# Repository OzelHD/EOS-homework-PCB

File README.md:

# Generation complete!
# EOS Homework Board

This board is a tutorial follow-along for the EOS homework assignment. It is designed to be a simple board that can be used to learn about PCB design and manufacturing. [Layout Video](https://www.youtube.com/watch?v=nkHFoxe0mrU), [PCB video](https://www.youtube.com/watch?v=PlXd3lLZ4vc)
:)
# Include documentation here

The documentation can be very similar to your wiki article

#Getting started

use `git submodule init && git submodule update --remote --recursive` to get the submodules, and then you can use the project as a normal KiCAD project.

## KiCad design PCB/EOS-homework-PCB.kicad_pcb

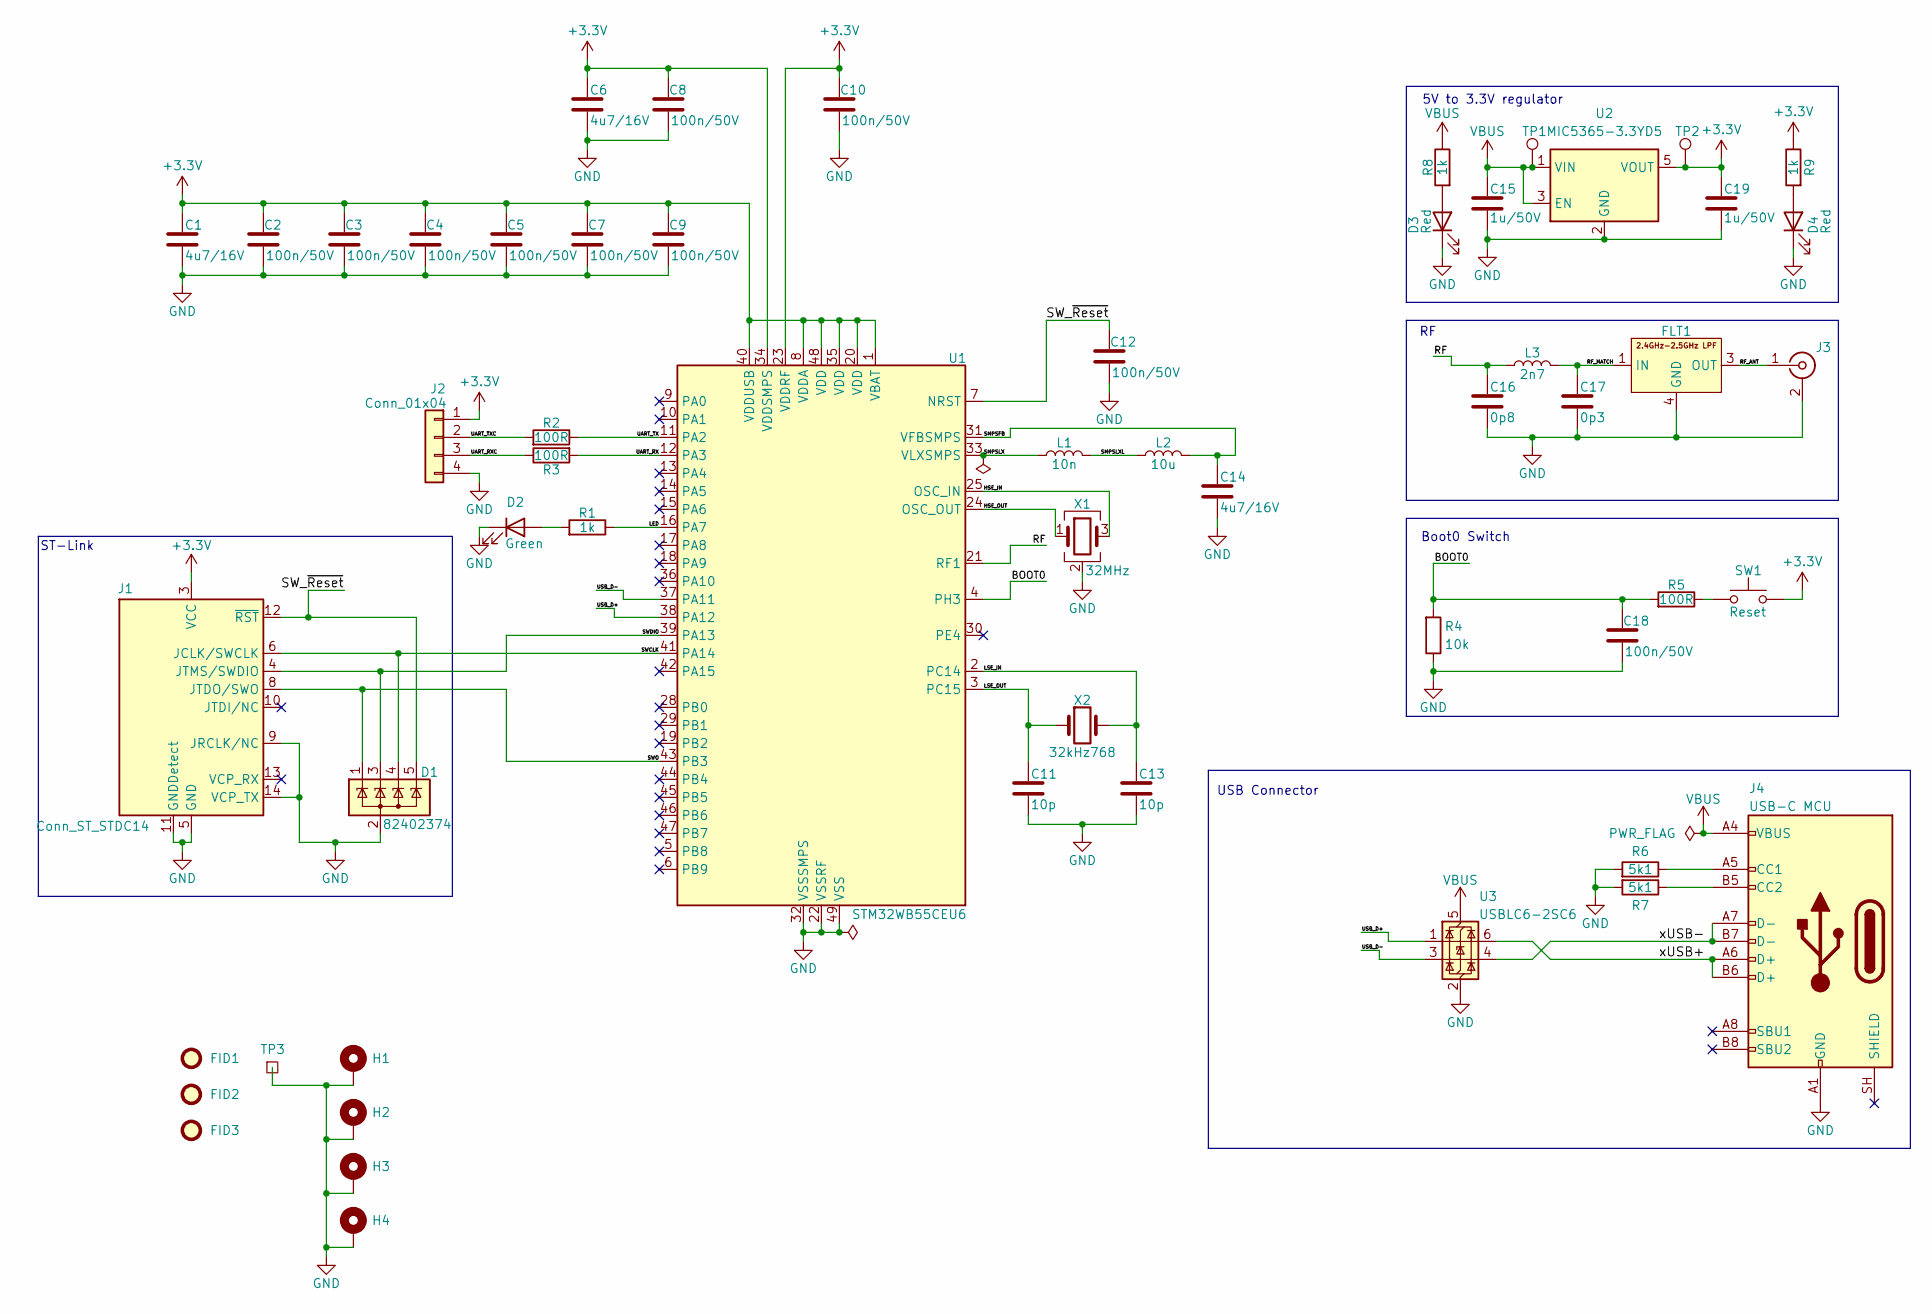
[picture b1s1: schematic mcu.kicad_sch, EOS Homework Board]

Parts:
C1, C6, C14: 4u7/16V; C_0805_2012Metric; Part No. 885012207053
C2, C3, C4, C5, C7, C8, C9, C10, C12, C18: 100n/50V; C_0603_1608Metric; Part No. 885012206095
C11, C13: 10p; C_0603_1608Metric
C15, C19: 1u/50V; C_0603_1608Metric; Part No. 885012206126
C16: 0p8; C_0603_1608Metric
C17: 0p3; C_0603_1608Metric
D1: 82402374; SOT-353_SC-70-5; Part No. 82402374
D2: Green; LED_0603_1608Metric; Part No. 150060GS75000
D3, D4: Red; LED_0603_1608Metric; Part No. 150060RS75000
FID1, FID2, FID3: Fiducial; Fiducial_1mm_Mask2mm
FLT1: DLF162500LT-5028A1
H1, H2, H3, H4: MountingHole_Pad; MountingHole_2.2mm_M2_Pad_Via
J1: Conn_ST_STDC14; IDC-Header_2x07_P1.27mm_Vertical_SMD; Part No. 62701420621
J2: Conn_01x04; Molex_PicoBlade_53048-0410_1x04_P1.25mm_Horizontal
J3: Conn_Coaxial; U.FL_Hirose_U.FL-R-SMT-1_Vertical
J4: USB-C MCU; USB_C_Receptacle_GCT_USB4105-xx-A_16P_TopMnt_Horizontal; Part No. 629722000214
L1: 10n; L_0402_1005Metric
L2: 10u; L_0805_2012Metric
L3: 2n7; L_0402_1005Metric
R1, R8, R9: 1k; R_0603_1608Metric; Part No. 560112116014
R2, R3, R5: 100R; R_0603_1608Metric; Part No. 560112116009
R4: 10k; R_0603_1608Metric; Part No. 560112116005
R6, R7: 5k1; R_0603_1608Metric; Part No. CRCW06035K10FKEAC
SW1: Reset; SW_Push_Wuerth_434123025826; Part No. 434123025826
TP1, TP2: TestPoint; TestPoint_Pad_D1.0mm
TP3: TestPoint_Square; TestPoint_THTPad_1.5x1.5mm_Drill0.7mm
U1: STM32WB55CEU6; QFN-48-1EP_7x7mm_P0.5mm_EP5.6x5.6mm
U2: MIC5365-3.3YD5; TSOT-23-5
U3: USBLC6-2SC6; SOT-23-6; Part No. 82400102
X1: 32MHz; Crystal_SMD_2016-4Pin_2.0x1.6mm
X2: 32kHz768; Crystal_SMD_2012-2Pin_2.0x1.2mm; Manifacturer Part Number STDMUB1-32.768K

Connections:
+3.3V: C1.1, C2.1, C3.1, C4.1, C5.1, C6.1, C7.1, C8.1, C9.1, C10.1, C19.1, J1.3 (VCC), J2.1, R9.2, SW1.2, TP2.1 (1_1), U1.1 (VBAT), U1.8 (VDDA), U1.20 (VDD), U1.23 (VDDRF), U1.34 (VDDSMPS), U1.35 (VDD), U1.40 (VDDUSB), U1.48 (VDD), U2.5 (VOUT)
/Microcontroller/BOOT0: C18.1, R4.1, R5.1, U1.4 (PH3)
/Microcontroller/HSE_IN: U1.25 (OSC_IN), X1.3
/Microcontroller/HSE_OUT: U1.24 (OSC_OUT), X1.1
/Microcontroller/LED: R1.2, U1.16 (PA7)
/Microcontroller/LSE_IN: C13.1, U1.2 (PC14), X2.2
/Microcontroller/LSE_OUT: C11.1, U1.3 (PC15), X2.1
/Microcontroller/RF: C16.1, L3.1, U1.21 (RF1)
/Microcontroller/RF_ANT: FLT1.3 (OUT), J3.1 (In)
/Microcontroller/RF_MATCH: C17.1, FLT1.1 (IN), L3.2
/Microcontroller/SMPSFB: C14.1, L2.2, U1.31 (VFBSMPS)
/Microcontroller/SMPSLX: L1.1, U1.33 (VLXSMPS)
/Microcontroller/SMPSLXL: L1.2, L2.1
/Microcontroller/SWCLK: D1.4 (K), J1.6 (JCLK/SWCLK), U1.41 (PA14)
/Microcontroller/SWDIO: D1.3 (K), J1.4 (JTMS/SWDIO), U1.39 (PA13)
/Microcontroller/SWO: D1.1 (K), J1.8 (JTDO/SWO), U1.43 (PB3)
/Microcontroller/SW_~Reset: C12.1, D1.5 (K), J1.12 (~RST), U1.7 (NRST)
/Microcontroller/UART_RX: R3.1, U1.12 (PA3)
/Microcontroller/UART_RXC: J2.3, R3.2
/Microcontroller/UART_TX: R2.2, U1.11 (PA2)
/Microcontroller/UART_TXC: J2.2, R2.1
/Microcontroller/USB_D+: U1.38 (PA12), U3.1 (I/O1)
/Microcontroller/USB_D-: U1.37 (PA11), U3.3 (I/O2)
/Microcontroller/xUSB+: J4.A6 (D+), J4.B6 (D+), U3.6 (I/O1)
/Microcontroller/xUSB-: J4.A7 (D-), J4.B7 (D-), U3.4 (I/O2)
GND: C1.2, C2.2, C3.2, C4.2, C5.2, C6.2, C7.2, C8.2, C9.2, C10.2, C11.2, C12.2, C13.2, C14.2, C15.2, C16.2, C17.2, C18.2, C19.2, D1.2 (A), D2.1 (K), D3.1 (K), D4.1 (K), FLT1.2 (GND), FLT1.4 (GND), H1.1 (1_1), H2.1 (1_1), H3.1 (1_1), H4.1 (1_1), J1.5 (GND), J1.7 (GND), J1.9 (JRCLK/NC), J1.11 (GNDDetect), J1.14 (VCP_TX), J2.4, J3.2 (Ext), J4.A1 (GND), J4.A12 (GND), J4.B1 (GND), J4.B12 (GND), R4.2, R6.1, R7.1, TP3.1 (1_1), U1.22 (VSSRF), U1.32 (VSSSMPS), U1.49 (VSS), U2.2 (GND), U3.2 (GND), X1.2 (G), X1.4 (G)
unnamed: D2.2 (A), R1.1
unnamed: D3.2 (A), R8.1
unnamed: D4.2 (A), R9.1
unnamed: J4.A5 (CC1), R6.2
unnamed: J4.B5 (CC2), R7.2
unnamed: R5.2, SW1.1
VBUS: C15.1, J4.A4 (VBUS), J4.A9 (VBUS), J4.B4 (VBUS), J4.B9 (VBUS), R8.2, TP1.1 (1_1), U2.1 (VIN), U2.3 (EN), U3.5 (VBUS)

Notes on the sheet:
Boot0 Switch
ST-Link
USB Connector
5V to 3.3V regulator

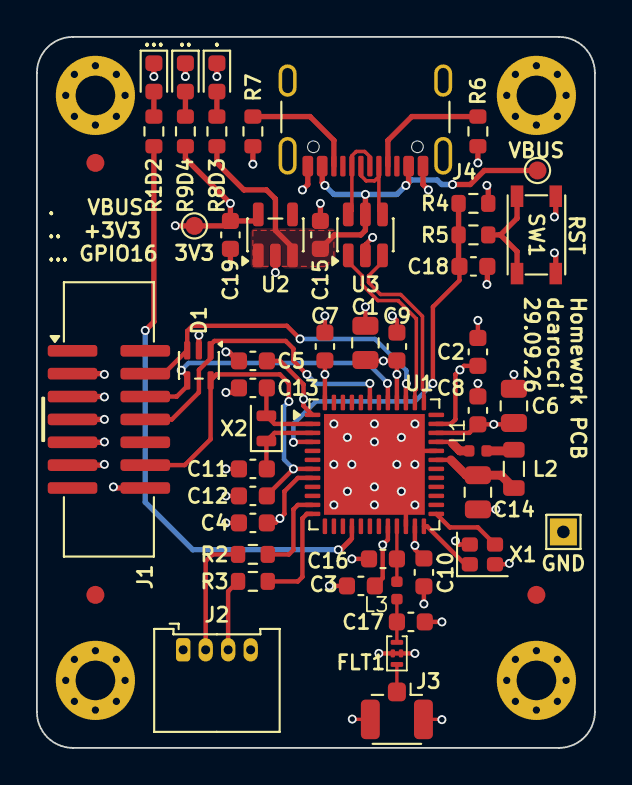
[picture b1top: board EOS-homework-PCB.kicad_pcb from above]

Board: 4 copper layers, 31.0 x 39.5 mm, 56 parts (0 on the bottom side), 33 nets.

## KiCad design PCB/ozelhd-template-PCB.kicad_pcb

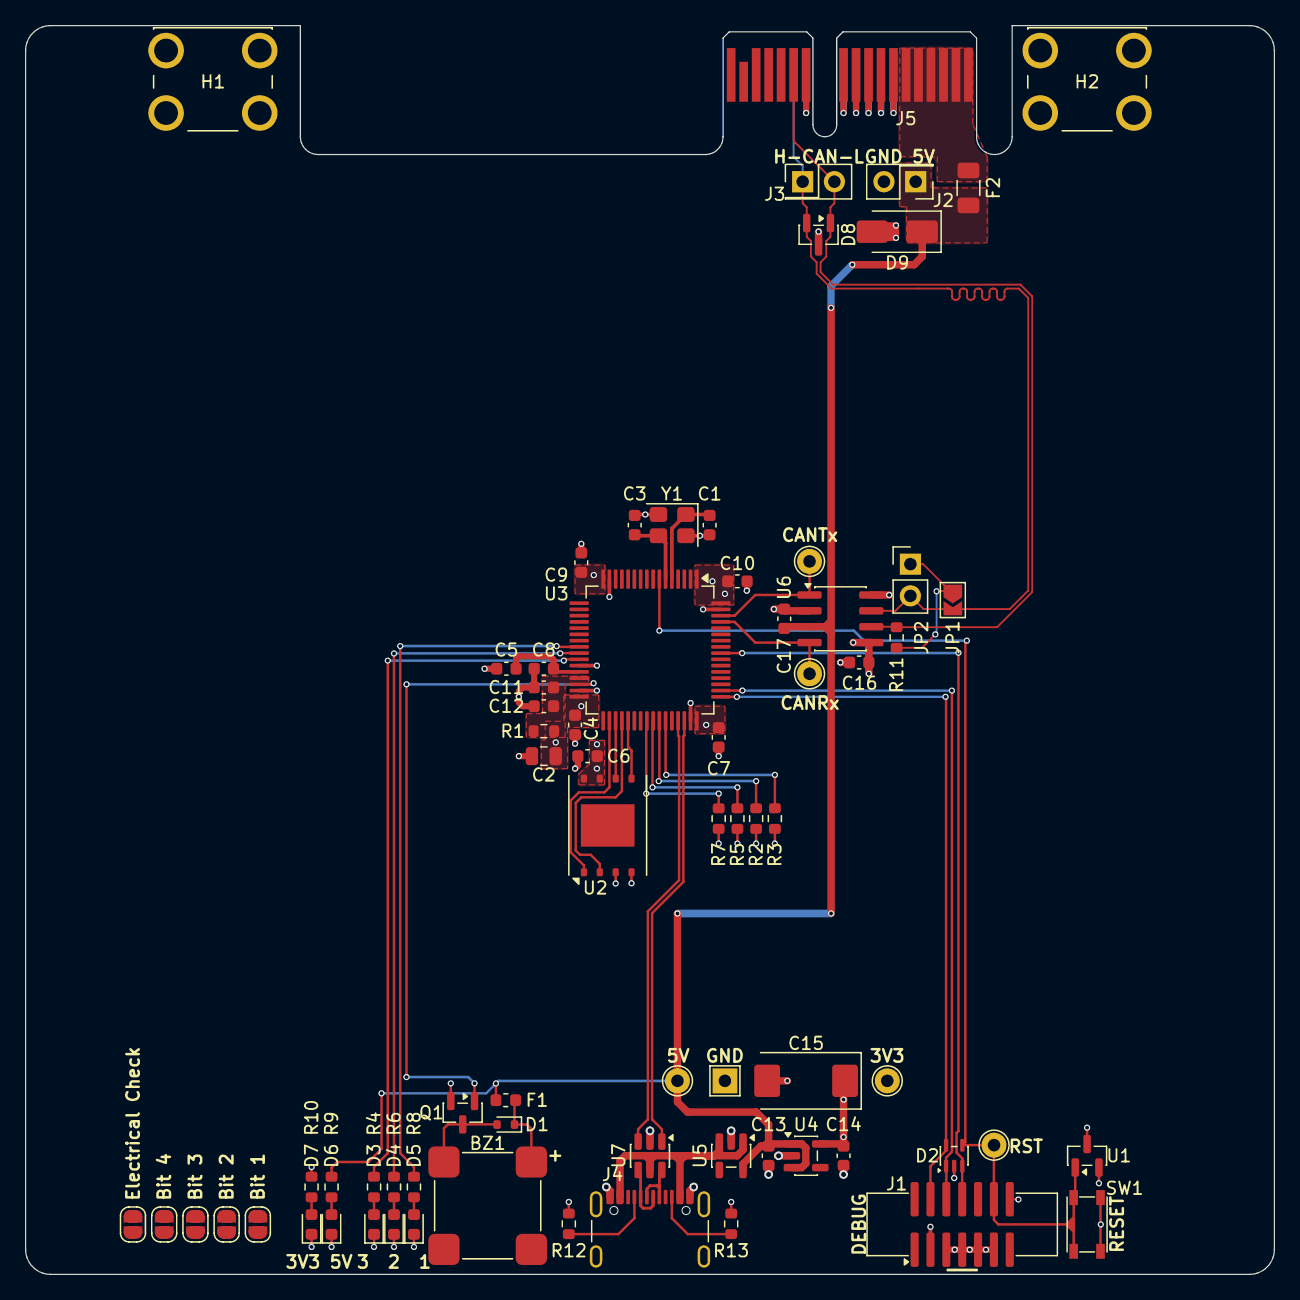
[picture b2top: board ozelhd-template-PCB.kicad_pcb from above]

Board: 4 copper layers, 100.0 x 100.0 mm, 72 parts (0 on the bottom side), 43 nets.

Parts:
BZ1: Buzzer; Buzzer_CUI_CMT-8504-100-SMT-TR
C1, C3: 10p/50V; C_0603_1608Metric
C2: 10u/10V; C_0805_2012Metric
C4, C6, C7, C8, C9, C10, C16, C17: 100n/50V; C_0603_1608Metric
C5, C12, C13, C14: 1u/16V; C_0603_1608Metric
C11: 10n/50V; C_0603_1608Metric
C15: 100u/6.3V; CP_EIA-7343-20_Kemet-V
D1: 10V; D_SOD-523
D2: 82402374; SOT-353_SC-70-5
D3, D6, D7: Red; LED_0603_1608Metric
D4: Yellow; LED_0603_1608Metric
D5: Green; LED_0603_1608Metric
D8: CAN TVS; SOT-23
D9: 5.0V; D_SMA
F1: 250mA/9V; Fuse_0603_1608Metric
F2: 1A/6V; Fuse_1206_3216Metric
H1, H2: 7790_NC; Mounting_Keystone_7790_NC
J1: STDC-14 Debug; IDC-Header_2x07_P1.27mm_Vertical_SMD
J2: 5V; PinHeader_2x01_P2.54mm_Vertical
J3: CAN; PinHeader_2x01_P2.54mm_Vertical
J4: USB-C MCU; USB_C_Receptacle_GCT_USB4105-xx-A_16P_TopMnt_Horizontal
J5: EdgeConn_FC; BUS_PCIexpress_x1
JP1: Termination; SolderJumper-2_P1.3mm_Open_TrianglePad1.0x1.5mm
JP2: DebugTermination; PinHeader_1x02_P2.54mm_Vertical
JP3: Assembly Done; SolderJumper-2_P1.3mm_Open_RoundedPad1.0x1.5mm
JP4: Numbering 1; SolderJumper-2_P1.3mm_Open_RoundedPad1.0x1.5mm
JP5: Numbering 2; SolderJumper-2_P1.3mm_Open_RoundedPad1.0x1.5mm
JP6: Numbering 3; SolderJumper-2_P1.3mm_Open_RoundedPad1.0x1.5mm
JP7: Numbering 4; SolderJumper-2_P1.3mm_Open_RoundedPad1.0x1.5mm
Q1: 2N7002; SOT-23
R1: 0R; R_0603_1608Metric
R2, R3, R5, R7: 2k2; R_0603_1608Metric
R4, R6, R8, R9, R10: 1k; R_0603_1608Metric
R11: 120R; R_0603_1608Metric
R12, R13: 5k1; R_0603_1608Metric
SW1: Reset; SW_Push_Wuerth_434123025826
TP1, TP2, TP3, TP4, TP5: TestPoint; TestPoint_THTPad_D2.0mm_Drill1.0mm
TP6: TestPoint; TestPoint_THTPad_2.0x2.0mm_Drill1.0mm
U1: ADM1818; SOT-23
U2: W25N512GVEIG; WSON-8-1EP_8x6mm_P1.27mm_EP3.4x4.3mm
U3: STM32G473RCTx; LQFP-64_10x10mm_P0.5mm
U4: AP2112K-3.3; SOT-23-5
U5: MAX40200AUK; SOT-23-5
U6: MCP2562-E-SN; SOIC-8_3.9x4.9mm_P1.27mm
U7: USBLC6-2SC6; SOT-23-6
Y1: 16MHz/8pF; Crystal_SMD_3225-4Pin_3.2x2.5mm

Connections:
+3.3V: C2.1, C4.1, C6.1, C7.1, C9.1, C10.1, C14.1, C15.1, C16.1, J1.3 (VCC), R1.2, R2.1, R3.1, R5.1, R7.1, R10.1, TP2.1 (1_1), U1.2 (VCC), U2.3 (~WP(IO2)), U2.7 (~HOLD(IO3)), U2.8 (VCC), U3.1 (VBAT), U3.16 (VDD), U3.32 (VDD), U3.48 (VDD), U3.64 (VDD), U4.5 (VOUT), U6.5 (Vio)
+3.3VA: C11.1, C12.1, R1.1, U3.29 (VDDA)
+5V: C13.1, C17.1, D9.1 (K), F1.1, F2.1, J2.1, R9.2, TP5.1 (1_1), U4.1 (VIN), U4.3 (EN), U5.5 (OUT), U6.3 (VDD)
/Backplane connector, mounting/5V_prefuse: F2.2, J5.B1 (5V), J5.B2 (5V), J5.B3 (5V), J5.B4 (5V), J5.B5 (5V), J5.B6 (5V)
/Backplane connector, mounting/CANH: D8.2 (K), J3.1, J5.A13 (CANH), JP1.2 (B), JP2.2 (B), U6.7 (CANH)
/Backplane connector, mounting/CANL: D8.1 (K), J3.2, J5.B13 (CANL), R11.1, U6.6 (CANL)
/CAN Transceiver/CAN.Rx: TP3.1 (1_1), U3.61 (PB8), U6.4 (RXD)
/CAN Transceiver/CAN.Tx: TP4.1 (1_1), U3.62 (PB9), U6.1 (TXD)
/Microcontroller/Buzzer_PWM: Q1.1 (G), U3.30 (PB10)
/Microcontroller/I2C2.SCL: R3.2, U3.43 (PA9)
/Microcontroller/I2C2.SDA: R2.2, U3.42 (PA8)
/Microcontroller/I2C3.SCL: R7.2, U3.40 (PC8)
/Microcontroller/I2C3.SDA: R5.2, U3.41 (PC9)
/Microcontroller/LED1: R8.1, U3.24 (PB0)
/Microcontroller/LED2: R6.1, U3.25 (PB1)
/Microcontroller/LED3: R4.1, U3.26 (PB2)
/Microcontroller/OSC_IN: C1.1, U3.5 (PF0), Y1.1
/Microcontroller/OSC_OUT: C3.1, U3.6 (PF1), Y1.3
/Microcontroller/SPI2.CS: U2.1 (~CS), U3.34 (PB12)
/Microcontroller/SPI2.MISO: U2.2 (DO(IO1)), U3.36 (PB14)
/Microcontroller/SPI2.MOSI: U2.5 (DI(IO0)), U3.37 (PB15)
/Microcontroller/SPI2.SCK: U2.6 (CLK), U3.35 (PB13)
/Microcontroller/SWCLK: D2.1 (K), J1.6 (JCLK/SWCLK), U3.50 (PA14)
/Microcontroller/SWDIO: D2.5 (K), J1.4 (JTMS/SWDIO), U3.49 (PA13)
/Microcontroller/SWO: D2.3 (K), J1.8 (JTDO/SWO), U3.56 (PB3)
/Microcontroller/USB+: U3.46 (PA12), U7.1 (I/O1)
/Microcontroller/USB-: U3.45 (PA11), U7.3 (I/O2)
/Microcontroller/VREF: C5.1, C8.1, U3.28 (VREF+)
/Microcontroller/~Reset: D2.4 (K), J1.12 (~RST), SW1.1, TP1.1 (1_1), U1.1 (~RESET), U3.7 (PG10)
/USB Connector/xUSB+: J4.A6 (D+), J4.B6 (D+), U7.6 (I/O1)
/USB Connector/xUSB-: J4.A7 (D-), J4.B7 (D-), U7.4 (I/O2)
GND: C1.2, C2.2, C3.2, C4.2, C5.2, C6.2, C7.2, C8.2, C9.2, C10.2, C11.2, C12.2, C13.2, C14.2, C15.2, C16.2, C17.2, D2.2 (A), D3.1 (K), D4.1 (K), D5.1 (K), D6.1 (K), D7.1 (K), D8.3 (A), D9.2 (A), J1.5 (GND), J1.7 (GND), J1.9 (JRCLK/NC), J1.11 (GNDDetect), J1.14 (VCP_TX), J2.2, J4.A1 (GND), J4.A12 (GND), J4.B1 (GND), J4.B12 (GND), J5.A7 (GND), J5.A8 (GND), J5.A9 (GND), J5.A10 (GND), J5.A11 (GND), J5.A12 (GND), J5.B7 (GND), J5.B8 (GND), J5.B9 (GND), J5.B10 (GND), J5.B11 (GND), J5.B12 (GND), Q1.2 (S), R12.1, R13.1, SW1.2, TP6.1 (1_1), U1.3 (GND), U2.4 (GND), U3.15 (VSS), U3.27 (VSSA), U3.31 (VSS), U3.47 (VSS), U3.63 (VSS), U4.2 (GND), U5.2 (GND), U6.2 (VSS), U6.8 (STBY), U7.2 (GND), Y1.2, Y1.4
unnamed: BZ1.1 (+), D1.1 (K), F1.2
unnamed: BZ1.2 (-), D1.2 (A), Q1.3 (D)
unnamed: D3.2 (A), R4.2
unnamed: D4.2 (A), R6.2
unnamed: D5.2 (A), R8.2
unnamed: D6.2 (A), R9.1
unnamed: D7.2 (A), R10.2
unnamed: J4.A5 (CC1), R12.2
unnamed: J4.B5 (CC2), R13.2
unnamed: JP1.1 (A), JP2.1 (A), R11.2
VBUS: J4.A4 (VBUS), J4.A9 (VBUS), J4.B4 (VBUS), J4.B9 (VBUS), U5.1 (VDD), U5.3 (EN), U7.5 (VBUS)

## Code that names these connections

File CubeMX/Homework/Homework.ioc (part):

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Mcu.Name=STM32WB55CEUx
Mcu.Package=UFQFPN48
Mcu.UserName=STM32WB55CEUx
PA11.Mode=Device
PA11.Signal=USB_DM
PA12.Mode=Device
PA12.Signal=USB_DP
PA13.Mode=Trace_Asynchronous_SW
PA13.Signal=SYS_JTMS-SWDIO
PA14.Mode=Trace_Asynchronous_SW
PA14.Signal=SYS_JTCK-SWCLK
PA2.Mode=Asynchronous
PA2.Signal=LPUART1_TX
PA3.Mode=Asynchronous
PA3.Signal=LPUART1_RX
PA7.Signal=S_TIM17_CH1
PB3.Mode=Trace_Asynchronous_SW
PB3.Signal=SYS_JTDO-SWO
PC14-OSC32_IN.Mode=LSE-External-Oscillator
PC14-OSC32_IN.Signal=RCC_OSC32_IN
PC15-OSC32_OUT.Mode=LSE-External-Oscillator
PC15-OSC32_OUT.Signal=RCC_OSC32_OUT
RCC.HSE_VALUE=32000000
board=custom
